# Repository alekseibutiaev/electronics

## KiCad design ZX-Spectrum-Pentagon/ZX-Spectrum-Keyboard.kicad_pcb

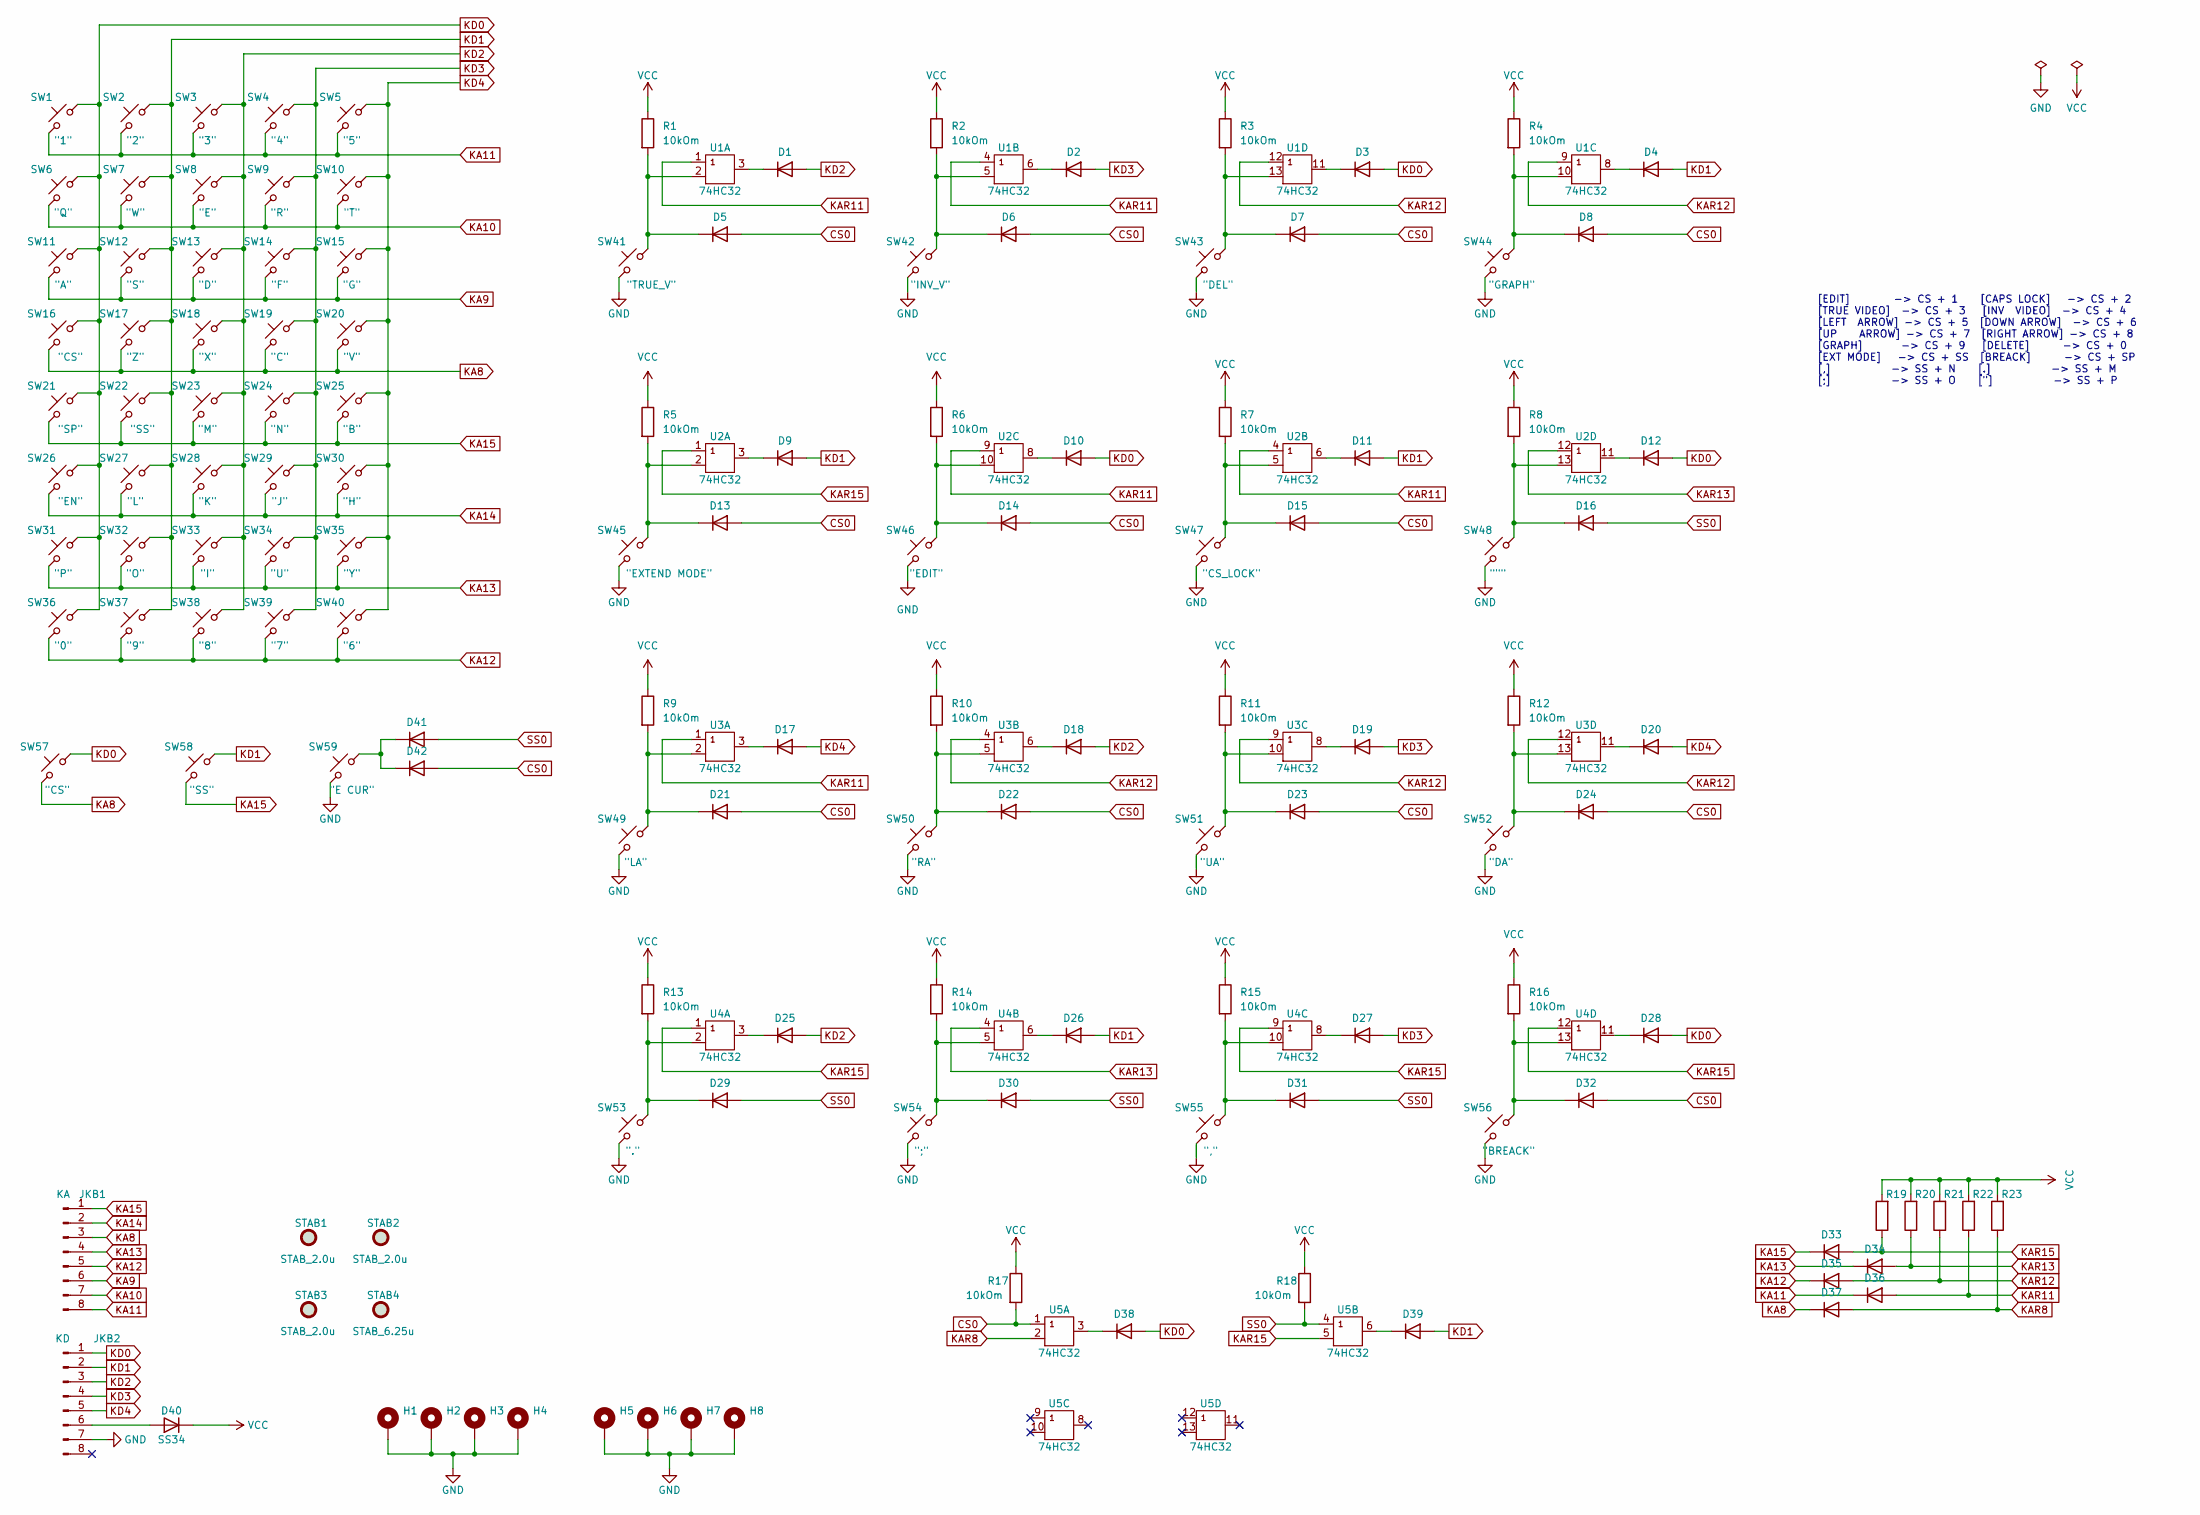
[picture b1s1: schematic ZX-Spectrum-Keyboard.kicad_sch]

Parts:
D1, D2, D3, D4, D5, D6, D7, D8, D9, D10, D11, D12, D13, D14, D15, D16, D17, D18, D19, D20, D21, D22, D23, D24, D25, D26, D27, D28, D29, D30, D31, D32, D33, D34, D35, D36, D37, D38, D39, D41, D42: 1N4148; D_MiniMELF
D40: SS34; D_SMA_Handsoldering
H1, H2, H3, H4, H5, H6, H7, H8: MountingHole_Pad; MountingHole_2.5mm_Pad_Via
JKB1: KA; PinHeader_1x08_P2.54mm_Vertical
JKB2: KD; PinHeader_1x08_P2.54mm_Vertical
R1, R2, R3, R4, R5, R6, R7, R8, R9, R10, R11, R12, R13, R14, R15, R16, R17, R18, R19, R20, R21, R22, R23: 10kOm; R_0805_2012Metric_Pad1.20x1.40mm_HandSolder
STAB1, STAB2, STAB3: STAB_2.0u; Stabilizer_Cherry_MX_2.00u
STAB4: STAB_6.25u; Stabilizer_Cherry_MX_6.25u
SW1, SW2, SW3, SW4, SW5, SW6, SW7, SW8, SW9, SW10, SW11, SW12, SW13, SW14, SW15, SW17, SW18, SW19, SW20, SW23, SW24, SW25, SW27, SW28, SW29, SW30, SW31, SW32, SW33, SW34, SW35, SW36, SW37, SW38, SW39, SW40, SW41, SW42, SW44, SW46, SW47, SW49, SW50, SW51, SW52, SW53, SW55, SW57, SW58: SW_Push_45deg; SW_Kailh_Cherry_MX_Universal_1.00u
SW16, SW56: SW_Push_45deg; SW_Kailh_Cherry_MX_Universal_2.00u
SW21: SW_Push_45deg; SW_Kailh_Cherry_MX_Universal_6.25u
SW22, SW48, SW54: SW_Push_45deg; SW_Kailh_Cherry_MX_Universal_1.25u
SW26: SW_Push_45deg; SW_Kailh_Cherry_MX_Universal_2.25u
SW43, SW59: SW_Push_45deg; SW_Kailh_Cherry_MX_Universal_1.50u
SW45: SW_Push_45deg; SW_Kailh_Cherry_MX_Universal_1.75u
U1, U2, U3, U4, U5: 74HC32; SOIC-14_3.9x8.7mm_P1.27mm

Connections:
CS0: D5.2 (A), D6.2 (A), D7.2 (A), D8.2 (A), D13.2 (A), D14.2 (A), D15.2 (A), D21.2 (A), D22.2 (A), D23.2 (A), D24.2 (A), D32.2 (A), D42.2 (A), R17.2, U5.1 (A)
GND: H1.1, H2.1, H3.1, H4.1, H5.1, H6.1, H7.1, H8.1, JKB2.7, SW41.2, SW42.2, SW43.2, SW44.2, SW45.2, SW46.2, SW47.2, SW48.2, SW49.2, SW50.2, SW51.2, SW52.2, SW53.2, SW54.2, SW55.2, SW56.2, SW59.2, U1.7 (GND), U2.7 (GND), U3.7 (GND), U4.7 (GND), U5.7 (GND)
KA8: D37.1 (K), JKB1.3, SW16.2, SW17.2, SW18.2, SW19.2, SW20.2, SW57.2
KA9: JKB1.6, SW11.2, SW12.2, SW13.2, SW14.2, SW15.2
KA10: JKB1.7, SW6.2, SW7.2, SW8.2, SW9.2, SW10.2
KA11: D36.1 (K), JKB1.8, SW1.2, SW2.2, SW3.2, SW4.2, SW5.2
KA12: D35.1 (K), JKB1.5, SW36.2, SW37.2, SW38.2, SW39.2, SW40.2
KA13: D34.1 (K), JKB1.4, SW31.2, SW32.2, SW33.2, SW34.2, SW35.2
KA14: JKB1.2, SW26.2, SW27.2, SW28.2, SW29.2, SW30.2
KA15: D33.1 (K), JKB1.1, SW21.2, SW22.2, SW23.2, SW24.2, SW25.2, SW58.2
KAR8: D37.2 (A), R23.1, U5.2 (B)
KAR11: D36.2 (A), R22.1, U1.1 (A), U1.4 (A), U2.4 (A), U2.9 (A), U3.1 (A)
KAR12: D35.2 (A), R21.1, U1.9 (A), U1.12 (A), U3.4 (A), U3.9 (A), U3.12 (A)
KAR13: D34.2 (A), R20.1, U2.12 (A), U4.4 (A)
KAR15: D33.2 (A), R19.1, U2.1 (A), U4.1 (A), U4.9 (A), U4.12 (A), U5.5 (B)
KD0: D3.2 (A), D10.2 (A), D12.2 (A), D28.2 (A), D38.2 (A), JKB2.1, SW1.1, SW6.1, SW11.1, SW16.1, SW21.1, SW26.1, SW31.1, SW36.1, SW57.1
KD1: D4.2 (A), D9.2 (A), D11.2 (A), D26.2 (A), D39.2 (A), JKB2.2, SW2.1, SW7.1, SW12.1, SW17.1, SW22.1, SW27.1, SW32.1, SW37.1, SW58.1
KD2: D1.2 (A), D18.2 (A), D25.2 (A), JKB2.3, SW3.1, SW8.1, SW13.1, SW18.1, SW23.1, SW28.1, SW33.1, SW38.1
KD3: D2.2 (A), D19.2 (A), D27.2 (A), JKB2.4, SW4.1, SW9.1, SW14.1, SW19.1, SW24.1, SW29.1, SW34.1, SW39.1
KD4: D17.2 (A), D20.2 (A), JKB2.5, SW5.1, SW10.1, SW15.1, SW20.1, SW25.1, SW30.1, SW35.1, SW40.1
unnamed: D1.1 (K), U1.3 (Y)
unnamed: D2.1 (K), U1.6 (Y)
unnamed: D3.1 (K), U1.11 (Y)
unnamed: D4.1 (K), U1.8 (Y)
unnamed: D5.1 (K), R1.2, SW41.1, U1.2 (B)
unnamed: D6.1 (K), R2.2, SW42.1, U1.5 (B)
unnamed: D7.1 (K), R3.2, SW43.1, U1.13 (B)
unnamed: D8.1 (K), R4.2, SW44.1, U1.10 (B)
unnamed: D9.1 (K), U2.3 (Y)
unnamed: D10.1 (K), U2.8 (Y)
unnamed: D11.1 (K), U2.6 (Y)
unnamed: D12.1 (K), U2.11 (Y)
unnamed: D13.1 (K), R5.2, SW45.1, U2.2 (B)
unnamed: D14.1 (K), R6.2, SW46.1, U2.10 (B)
unnamed: D15.1 (K), R7.2, SW47.1, U2.5 (B)
unnamed: D16.1 (K), R8.2, SW48.1, U2.13 (B)
unnamed: D17.1 (K), U3.3 (Y)
unnamed: D18.1 (K), U3.6 (Y)
unnamed: D19.1 (K), U3.8 (Y)
unnamed: D20.1 (K), U3.11 (Y)
unnamed: D21.1 (K), R9.2, SW49.1, U3.2 (B)
unnamed: D22.1 (K), R10.2, SW50.1, U3.5 (B)
unnamed: D23.1 (K), R11.2, SW51.1, U3.10 (B)
unnamed: D24.1 (K), R12.2, SW52.1, U3.13 (B)
unnamed: D25.1 (K), U4.3 (Y)
unnamed: D26.1 (K), U4.6 (Y)
unnamed: D27.1 (K), U4.8 (Y)
unnamed: D28.1 (K), U4.11 (Y)
unnamed: D29.1 (K), R13.2, SW53.1, U4.2 (B)
unnamed: D30.1 (K), R14.2, SW54.1, U4.5 (B)
unnamed: D31.1 (K), R15.2, SW55.1, U4.10 (B)
unnamed: D32.1 (K), R16.2, SW56.1, U4.13 (B)
unnamed: D38.1 (K), U5.3 (Y)
unnamed: D39.1 (K), U5.6 (Y)
unnamed: D40.2 (A), JKB2.6
unnamed: D41.1 (K), D42.1 (K), SW59.1
SS0: D16.2 (A), D29.2 (A), D30.2 (A), D31.2 (A), D41.2 (A), R18.2, U5.4 (A)
VCC: D40.1 (K), R1.1, R2.1, R3.1, R4.1, R5.1, R6.1, R7.1, R8.1, R9.1, R10.1, R11.1, R12.1, R13.1, R14.1, R15.1, R16.1, R17.1, R18.1, R19.2, R20.2, R21.2, R22.2, R23.2, U1.14 (VCC), U2.14 (VCC), U3.14 (VCC), U4.14 (VCC), U5.14 (VCC)

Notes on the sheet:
[EDIT] -> CS + 1 [CAPS LOCK] -> CS + 2 [TRUE VIDEO] -> CS + 3 [INV VIDEO] -> CS + 4 [LEFT ARROW] -> CS + 5 [DOWN ARROW] -> CS + 6 [UP ARROW] -> CS + 7 [RIGHT ARROW] -> CS + 8 [GRAPH] -> CS + 9 [DELETE] -> CS + 0 [EXT MODE] -> CS + SS [BREACK] -> CS + SP [,] -> SS + N [.] -> SS + M [;] -> SS + O ["]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

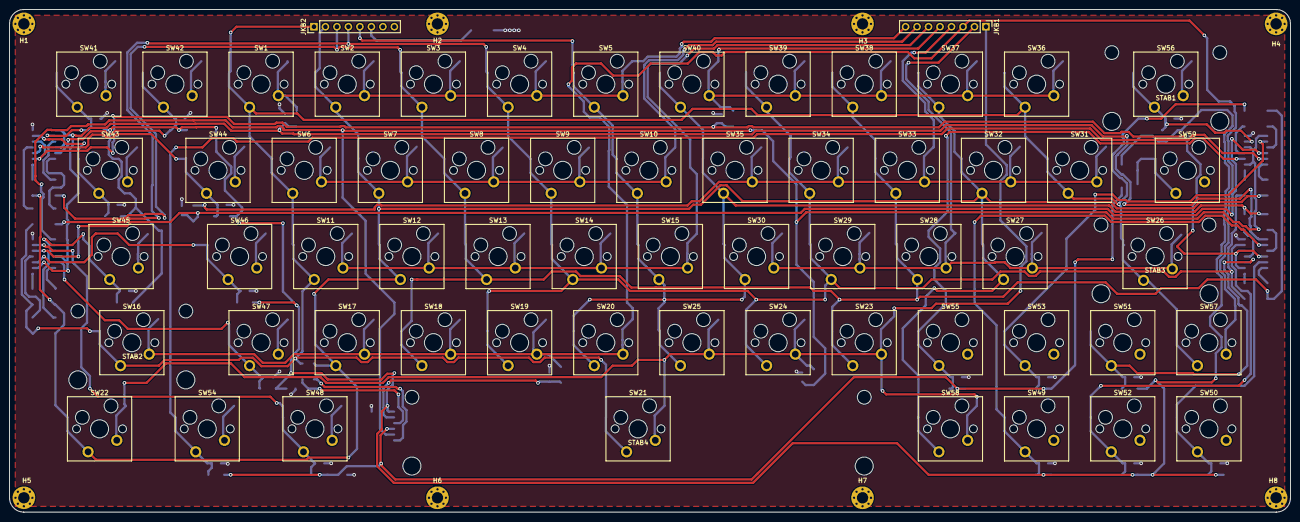
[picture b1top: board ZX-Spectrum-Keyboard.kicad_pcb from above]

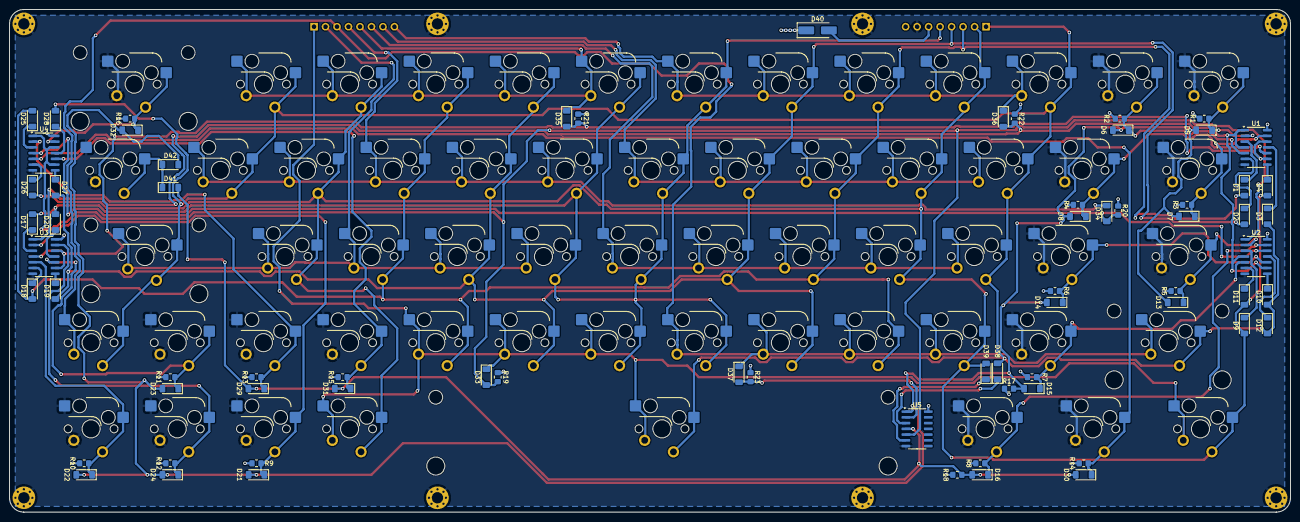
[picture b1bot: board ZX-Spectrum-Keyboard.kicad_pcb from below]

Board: 2 copper layers, 283.2 x 111.1 mm, 143 parts (70 on the bottom side), 58 nets.
